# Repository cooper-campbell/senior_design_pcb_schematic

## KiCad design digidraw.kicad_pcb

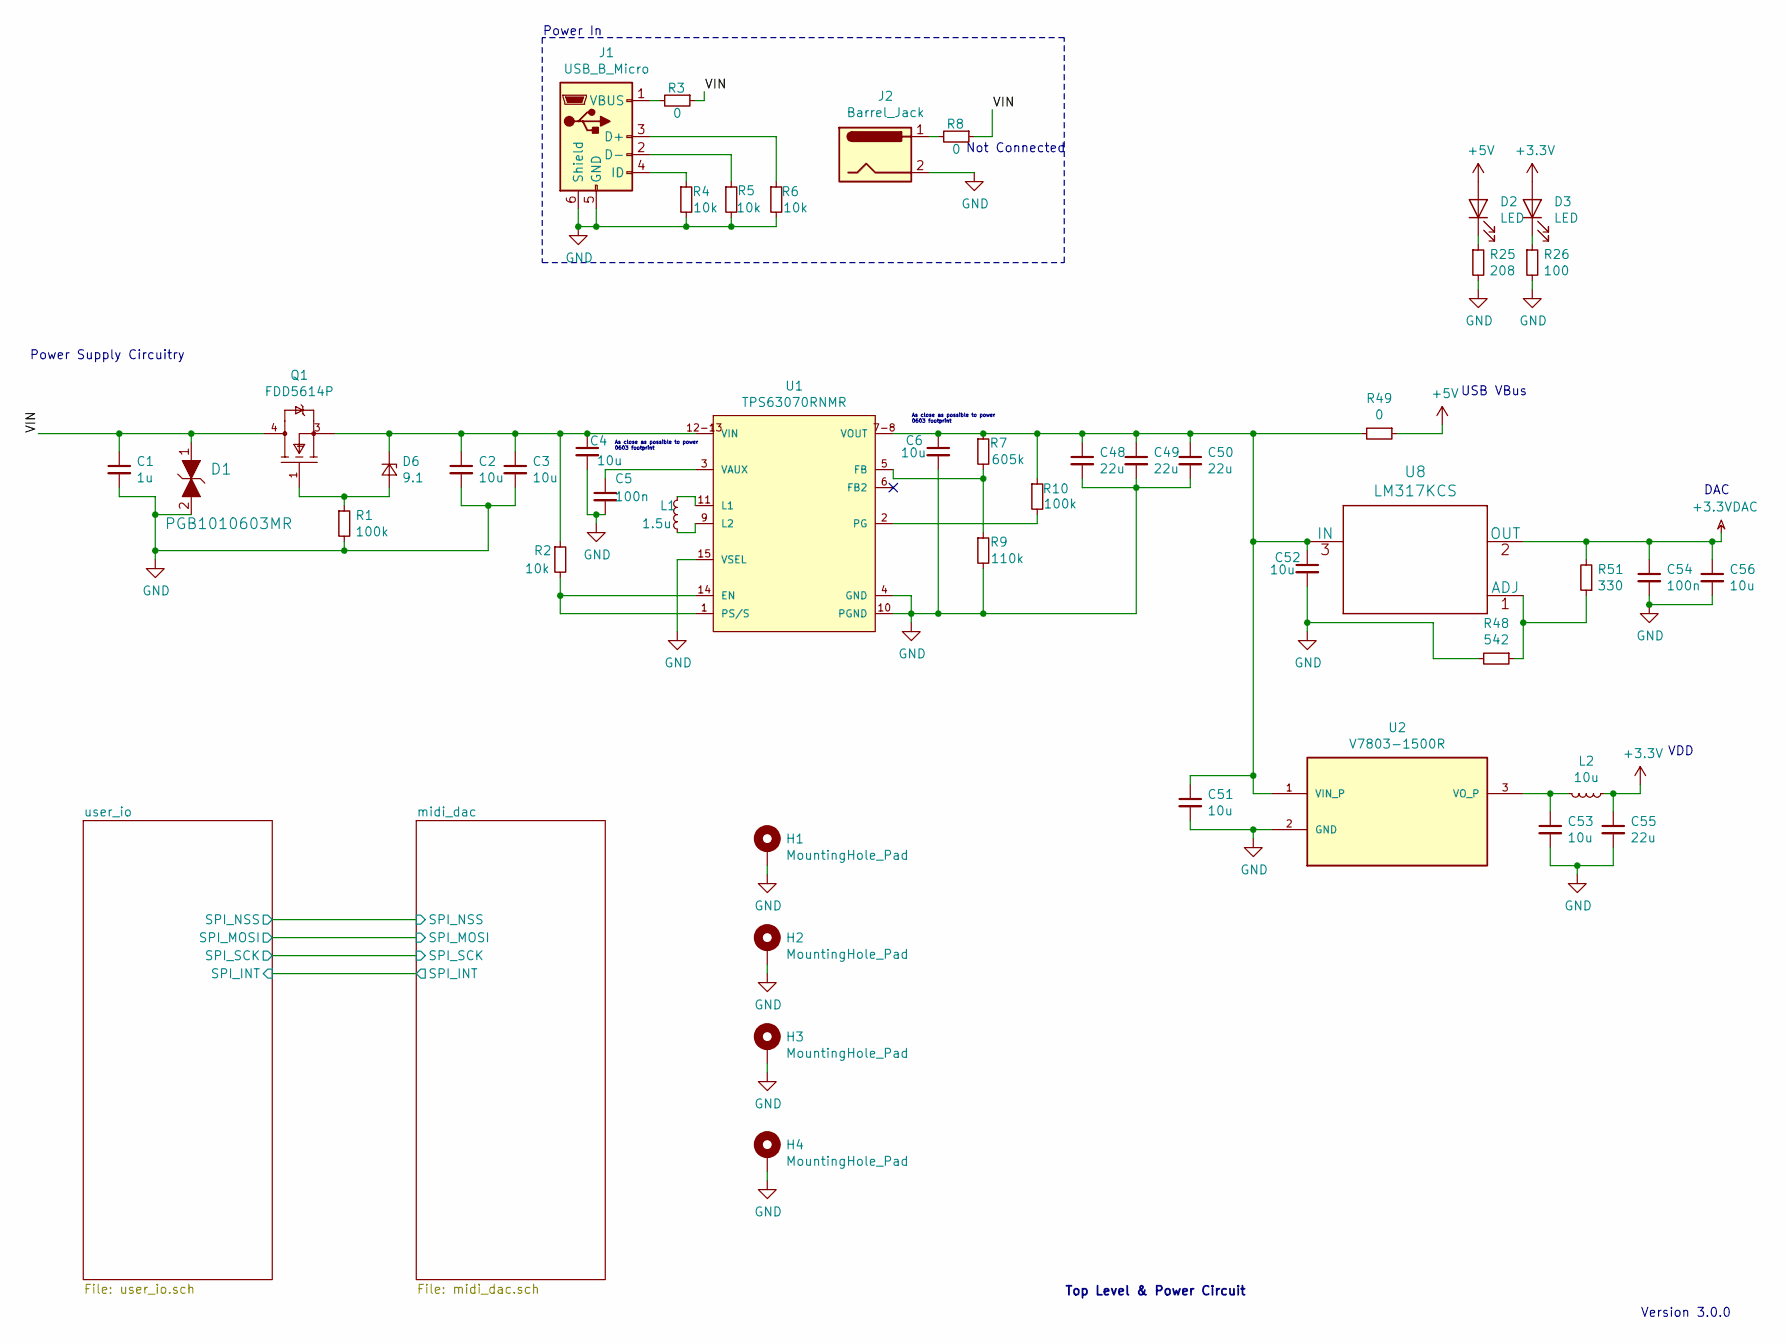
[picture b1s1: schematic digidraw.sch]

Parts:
C1: 1u; C_0805_2012Metric; Min Voltage Rating 16 V
C2, C3: 10u; C_0805_2012Metric; Min Voltage Rating 16 V
C4: 10u; C_0603_1608Metric; Min Voltage Rating 16 V
C5: 100n; C_0805_2012Metric; Min Voltage Rating 16 V
C6: 10u; C_0603_1608Metric; Min Voltage Rating 5.2 V
C48, C49, C50: 22u; C_0805_2012Metric; Min Voltage Rating 5.2 V
C51, C53: 10u; C_0603_1608Metric
C52: 10u; C_0805_2012Metric; Min Voltage Rating 5.2 V
C54: 100n; C_0805_2012Metric; Min Voltage Rating 3.3 V
C55: 22u; C_0603_1608Metric; Min Voltage Rating 3.3 V
C56: 10u; C_0603_1608Metric; Min Voltage Rating 3.3 V
D1: PGB1010603MR; 0603; MPN PGB1010603MR; Digi-Key_PN F2594CT-ND
D2, D3: LED; LED_0603_1608Metric; Digi-Key_PN AA1608SURSK
D6: 9.1; D_0603_1608Metric; Digi-Key_PN CDBU0320
H1, H2, H3, H4: MountingHole_Pad; MountingHole_4.3mm_M4_Pad_Via
J1: USB_B_Micro; USB_Micro-B_Molex-105017-0001; Digi-Key_PN 105017-0001
J2: Barrel_Jack; Barrel_Jack_5.5mmODx2.1mmID_PJ-202A; Digi-Key_PN PJ-202A
L1: 1.5u; InductorWEPD; Digi-Key_PN 7447707015
L2: 10u; L_0603_1608Metric; Digi-Key_PN MLZ1608E100MT
Q1: FDD5614P; ON_Semi-369AS-09_2016-O-0; mouser part number 512-FDD5614P; digikey description MOSFET P-CH 60V 15A DPAK
R1, R10: 100k; R_0603_1608Metric
R2, R4, R5, R6: 10k; R_0603_1608Metric
R3, R8, R49: 0; R_0603_1608Metric
R7: 605k; R_0603_1608Metric
R9: 110k; R_0603_1608Metric
R25: 208; R_0603_1608Metric
R26: 100; R_0603_1608Metric
R48: 542; R_0603_1608Metric
R51: 330; R_0603_1608Metric
U1: TPS63070RNMR; Texas_Instruments-RNM0015A-0-0-MFG; output voltage 2.5-9V; mouser part number 595-TPS63070RNMR; digikey description IC REG BCK BST ADJ 3.6A 15VQFN
U2: V7803-1500R; CONV_V7803-1500R; PARTREV 1.03; Digi-Key_PN V7803-1500R
U8: LM317KCS; Digi-Key_PN LM317KCS

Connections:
+3.3VDAC: C54.1, C56.1, R51.2, U8.2 (OUT); also elsewhere on the board
+3V3: C55.1, D3.2 (A), L2.1; also elsewhere on the board
+5V: D2.2 (A), R49.1; also elsewhere on the board
/VIN: C1.1, D1.1, Q1.4 (D), R3.1, R8.1
GND: C1.2, C2.2, C3.2, C4.2, C5.2, C6.2, C48.2, C49.2, C50.2, C51.2, C52.2, C53.2, C54.2, C55.2, C56.2, D1.2, H1.1, H2.1, H3.1, H4.1, J1.5 (GND), J1.6 (Shield), J2.2, R1.2, R4.2, R5.2, R6.2, R9.2, R25.2, R26.2, R48.2, U1.4 (GND), U1.10 (PGND), U1.15 (VSEL), U2.2 (GND); also elsewhere on the board
unnamed: C2.1, C3.1, C4.1, D6.1 (K), Q1.3 (S), R2.1, U1.12-13 (VIN)
unnamed: C5.1, U1.3 (VAUX)
unnamed: C6.1, C48.1, C49.1, C50.1, C51.1, C52.1, R7.1, R10.1, R49.2, U1.7-8 (VOUT), U2.1 (VIN_P), U8.3 (IN)
unnamed: C53.1, L2.2, U2.3 (VO_P)
unnamed: D2.1 (K), R25.1
unnamed: D3.1 (K), R26.1
unnamed: D6.2 (A), Q1.1 (G), R1.1
unnamed: J1.1 (VBUS), R3.2
unnamed: J1.2 (D-), R5.1
unnamed: J1.3 (D+), R6.1
unnamed: J1.4 (ID), R4.1
unnamed: J2.1, R8.2
unnamed: L1.1, U1.9 (L2)
unnamed: L1.2, U1.11 (L1)
unnamed: R2.2, U1.1 (PS/S), U1.14 (EN)
unnamed: R7.2, R9.1, U1.5 (FB)
unnamed: R10.2, U1.2 (PG)
unnamed: R48.1, R51.1, U8.1 (ADJ)

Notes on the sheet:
Power In
Top Level & Power Circuit
Version 3.0.0
Not Connected
As close as possible to power 0603 footprint
USB VBus
VDD
DAC
Power Supply Circuitry

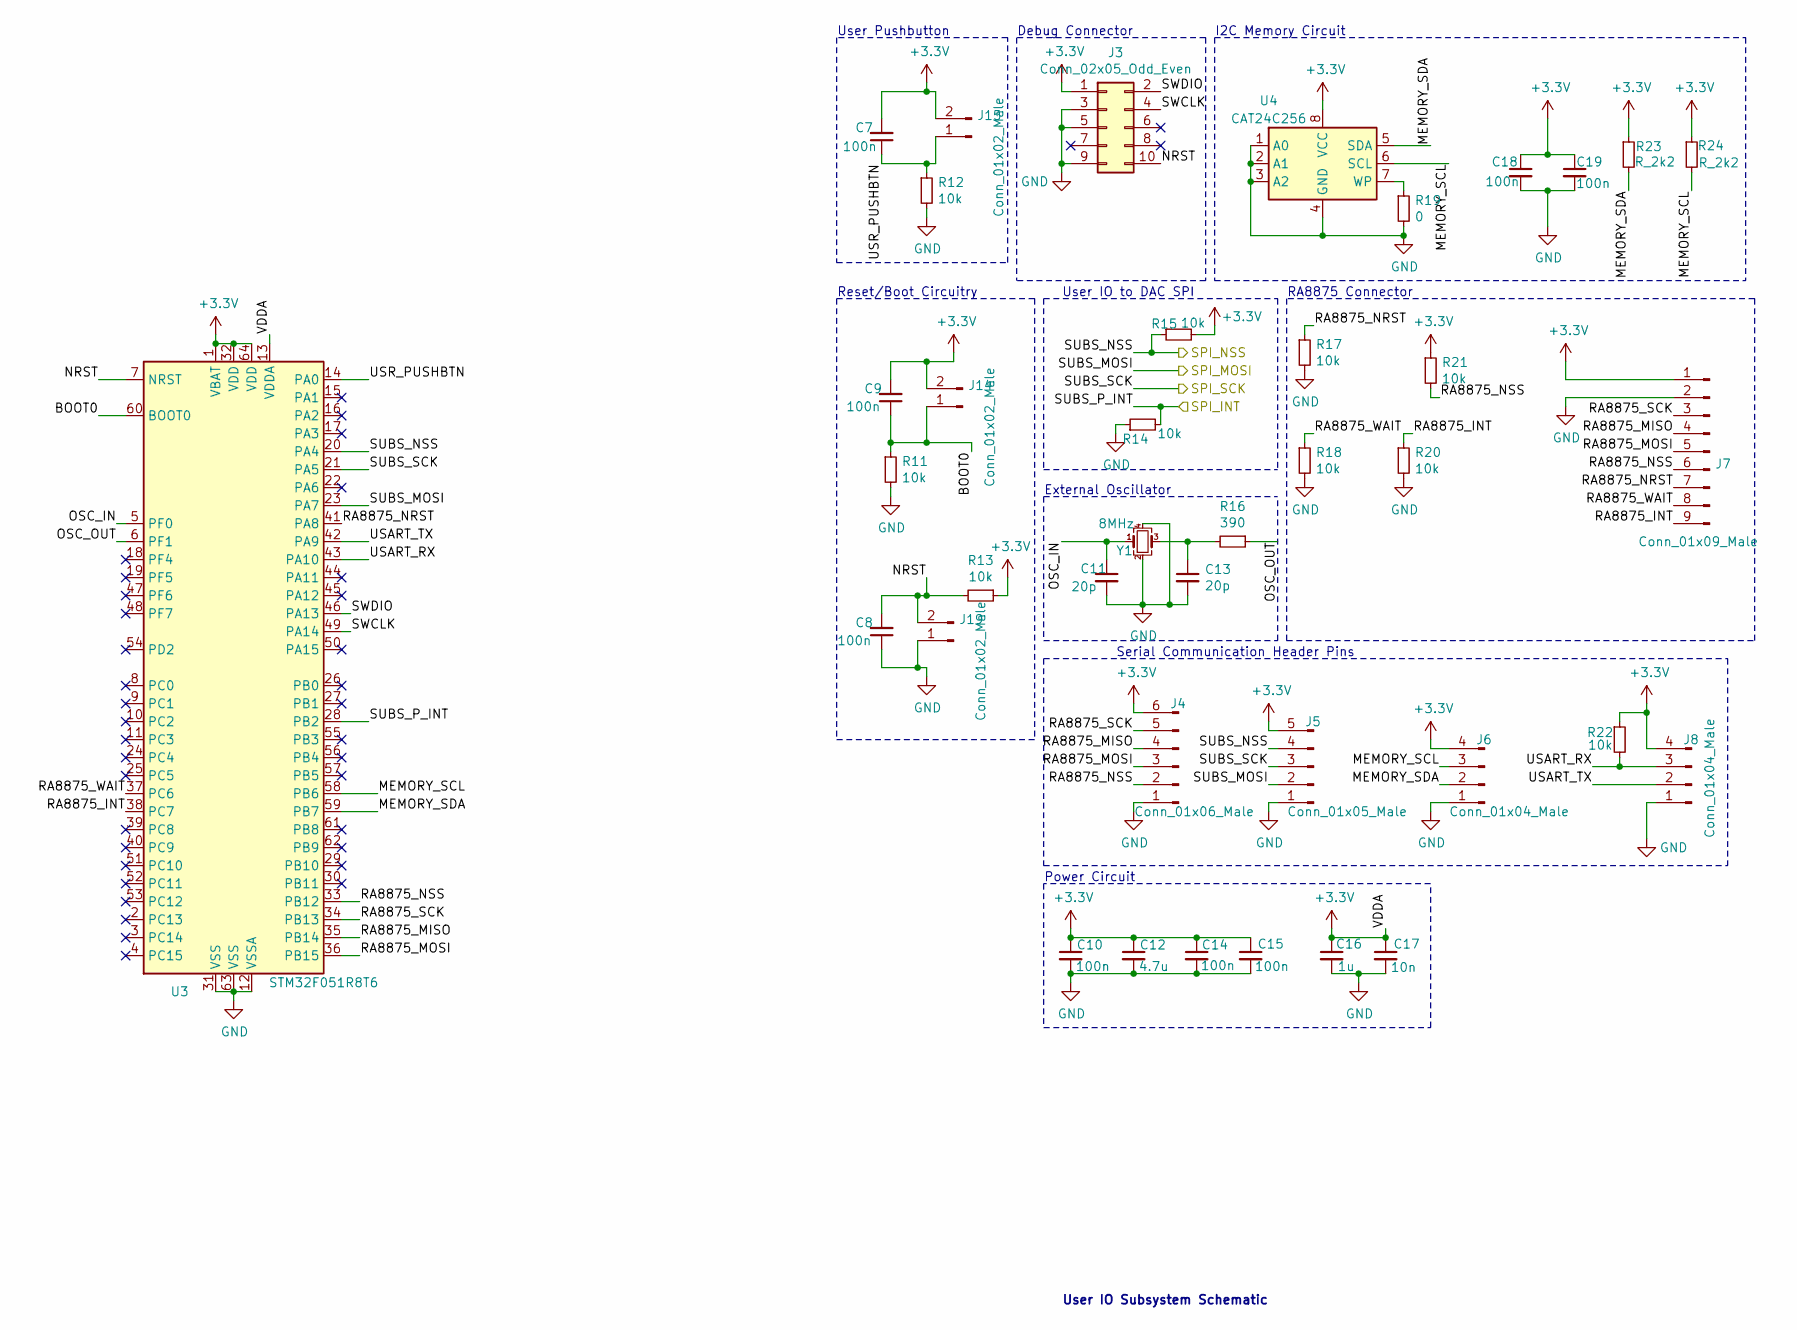
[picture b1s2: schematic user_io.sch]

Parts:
C7, C8, C9: 100n; C_0805_2012Metric; Min Voltage Rating 3.3 V
C10, C14, C15, C18, C19: 100n; C_0603_1608Metric; Min Voltage Rating 3.3 V
C11, C13: 20p; C_0603_1608Metric; Min Voltage Rating 3.3 V
C12: 4.7u; C_0603_1608Metric; Min Voltage Rating 3.3 V
C16: 1u; C_0603_1608Metric; Min Voltage Rating 3.3 V
C17: 10n; C_0603_1608Metric
J3: Conn_02x05_Odd_Even; PinHeader_2x05_P1.27mm_Vertical_SMD
J4: Conn_01x06_Male; PinHeader_1x06_P2.54mm_Vertical
J5: Conn_01x05_Male; PinHeader_1x05_P2.54mm_Vertical
J6, J8: Conn_01x04_Male; PinHeader_1x04_P2.54mm_Vertical
J7: Conn_01x09_Male; PinHeader_1x09_P2.54mm_Vertical
J14, J15, J19: Conn_01x02_Male; PinHeader_1x02_P2.54mm_Vertical
R11, R12, R13, R14, R15, R17, R18, R20, R21, R22: 10k; R_0603_1608Metric
R16: 390; R_0603_1608Metric
R19: 0; R_0603_1608Metric
R23, R24: R_2k2; R_0603_1608Metric
U3: STM32F051R8T6; LQFP-64_10x10mm_P0.5mm; Digi-Key_PN STM32F051R8T6
U4: CAT24C256; TSSOP-8_4.4x3mm_P0.65mm; Digi-Key_PN CAT24C256YI-GT3
Y1: 8MHz; Crystal_SMD_Abracon_ABM10-4Pin_2.5x2.0mm; Digi-Key_PN ASDDV-8.000MHZ-LR-T

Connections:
+3V3: C7.2, C9.2, C10.1, C12.1, C14.1, C15.1, C16.1, C17.1, C18.1, C19.1, J3.1, J4.6, J5.5, J6.4, J7.1, J8.4, J14.2, J15.2, R13.1, R15.2, R21.1, R22.1, R23.1, R24.1, U3.1 (VBAT), U3.13 (VDDA), U3.32 (VDD), U3.64 (VDD), U4.8 (VCC); also elsewhere on the board
/midi_dac/SPI_INT: R14.2, U3.28 (PB2); also elsewhere on the board
/midi_dac/SPI_MOSI: J5.2, U3.23 (PA7); also elsewhere on the board
/midi_dac/SPI_NSS: J5.4, R15.1, U3.20 (PA4); also elsewhere on the board
/midi_dac/SPI_SCK: J5.3, U3.21 (PA5); also elsewhere on the board
/user_io/BOOT0: C9.1, J14.1, R11.1, U3.60 (BOOT0)
/user_io/MEMORY_SCL: J6.3, R24.2, U3.58 (PB6), U4.6 (SCL)
/user_io/MEMORY_SDA: J6.2, R23.2, U3.59 (PB7), U4.5 (SDA)
/user_io/NRST: C8.2, J3.10, J19.2, R13.2, U3.7 (NRST)
/user_io/OSC_IN: C11.1, U3.5 (PF0), Y1.1
/user_io/OSC_OUT: R16.1, U3.6 (PF1)
/user_io/RA8875_INT: J7.9, R20.1, U3.38 (PC7)
/user_io/RA8875_MISO: J4.4, J7.4, U3.35 (PB14)
/user_io/RA8875_MOSI: J4.3, J7.5, U3.36 (PB15)
/user_io/RA8875_NRST: J7.7, R17.1, U3.41 (PA8)
/user_io/RA8875_NSS: J4.2, J7.6, R21.2, U3.33 (PB12)
/user_io/RA8875_SCK: J4.5, J7.3, U3.34 (PB13)
/user_io/RA8875_WAIT: J7.8, R18.1, U3.37 (PC6)
/user_io/SWCLK: J3.4, U3.49 (PA14)
/user_io/SWDIO: J3.2, U3.46 (PA13)
/user_io/USART_RX: J8.3, R22.2, U3.43 (PA10)
/user_io/USART_TX: J8.2, U3.42 (PA9)
/user_io/USR_PUSHBTN: C7.1, J15.1, R12.1, U3.14 (PA0)
GND: C8.1, C10.2, C11.2, C12.2, C13.2, C14.2, C15.2, C16.2, C17.2, C18.2, C19.2, J3.3, J3.5, J3.9, J4.1, J5.1, J6.1, J7.2, J8.1, J19.1, R11.2, R12.2, R14.1, R17.2, R18.2, R19.2, R20.2, U3.12 (VSSA), U3.31 (VSS), U3.63 (VSS), U4.1 (A0), U4.2 (A1), U4.3 (A2), U4.4 (GND), Y1.2, Y1.4; also elsewhere on the board
unnamed: C13.1, R16.2, Y1.3
unnamed: R19.1, U4.7 (WP)

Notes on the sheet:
I2C Memory Circuit
User IO to DAC SPI
RA8875 Connector
User IO Subsystem Schematic
Reset/Boot Circuitry
Debug Connector
Power Circuit
Serial Communication Header Pins
External Oscillator
User Pushbutton

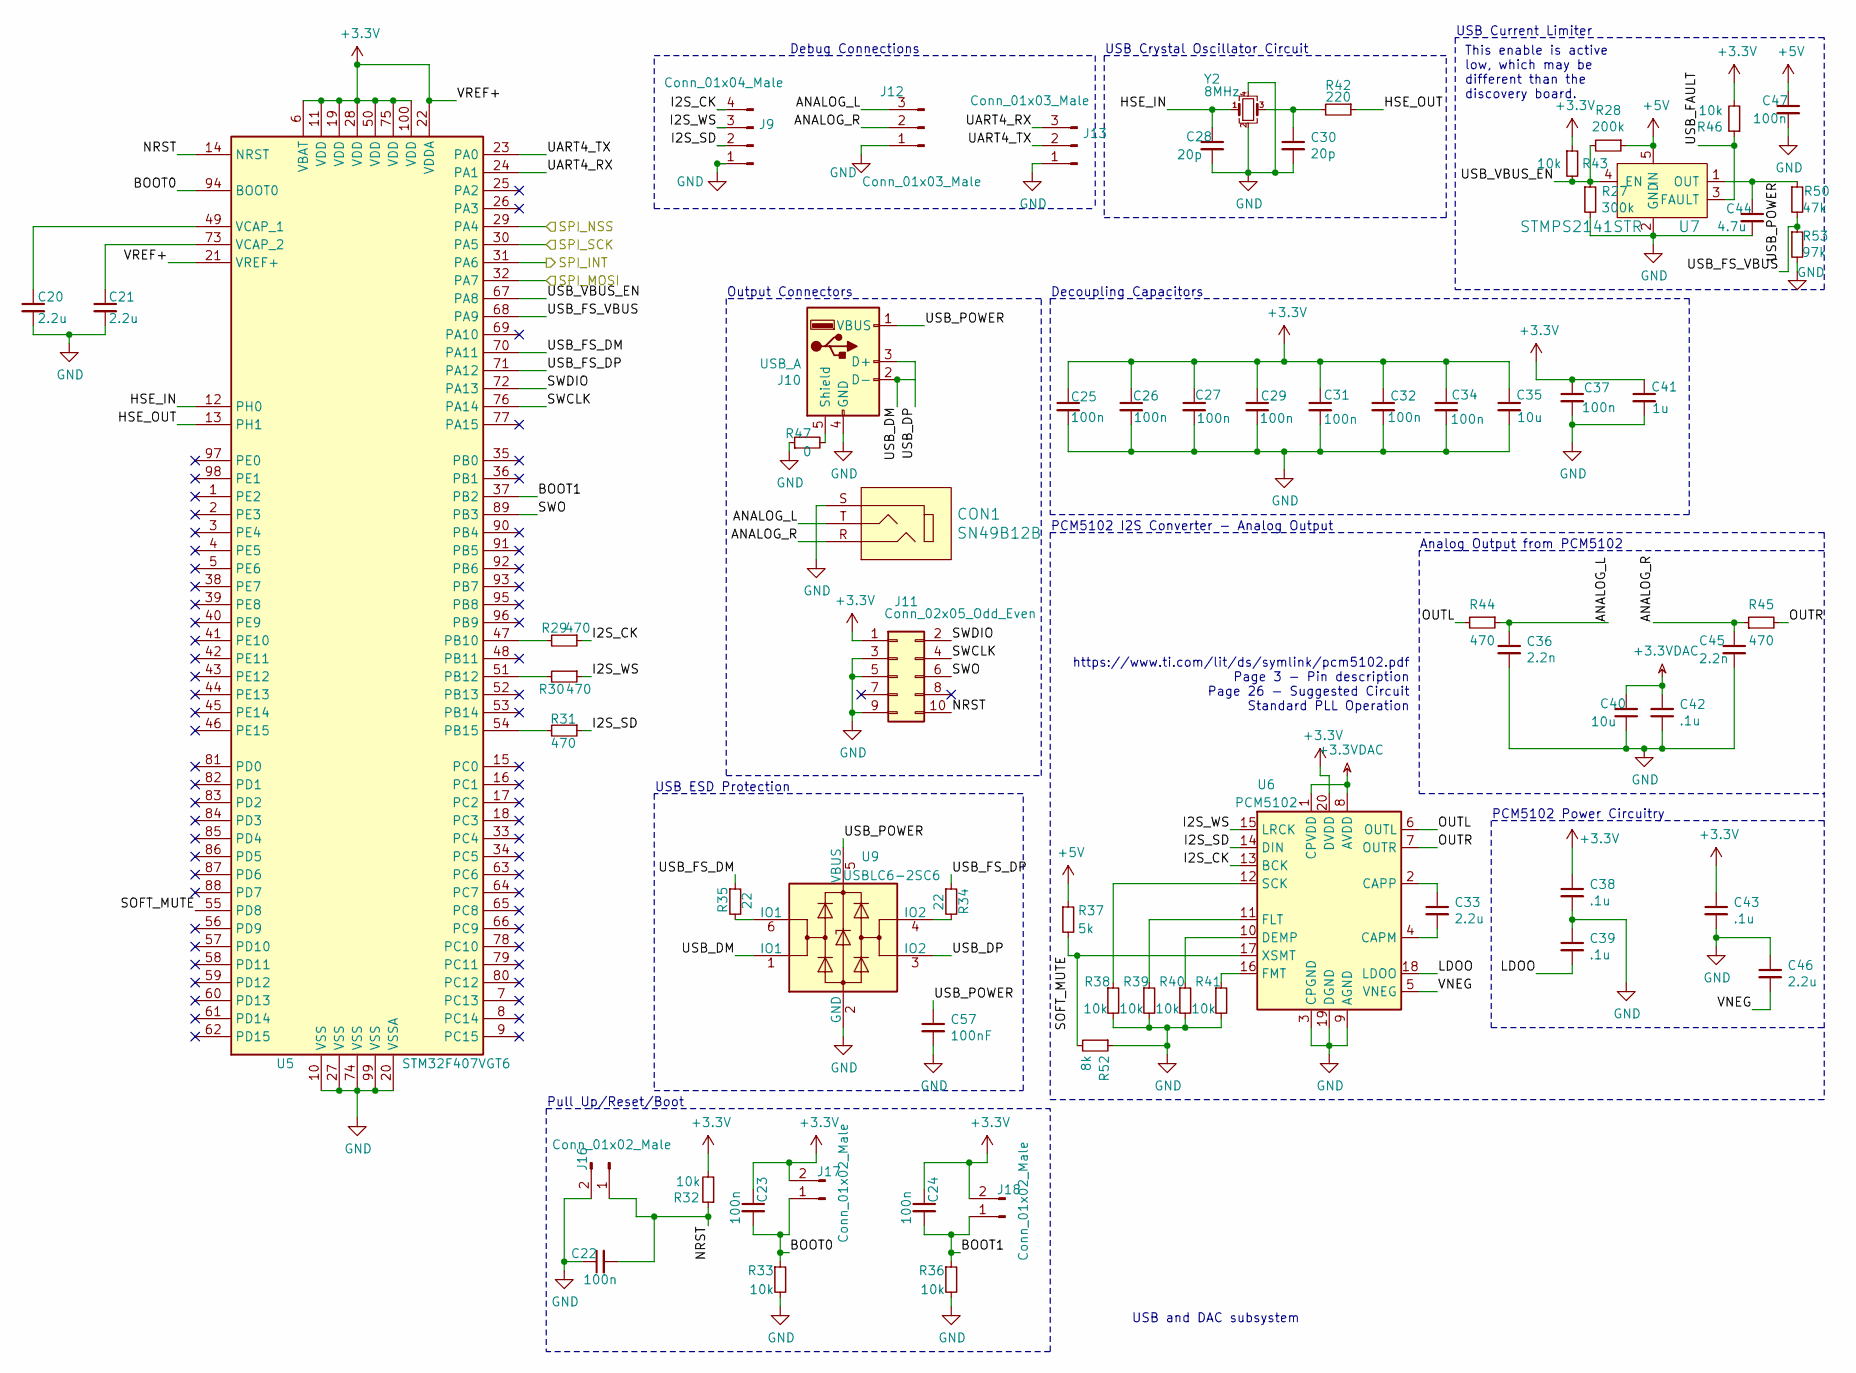
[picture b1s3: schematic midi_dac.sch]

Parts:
C20, C21, C46: 2.2u; C_0805_2012Metric; Min Voltage Rating 3.3 V
C22, C23, C24, C25, C26, C27, C29, C31, C32, C34, C37: 100n; C_0805_2012Metric; Min Voltage Rating 3.3 V
C28, C30: 20p; C_0603_1608Metric; Min Voltage Rating 3.3 V
C33: 2.2u; C_0603_1608Metric; Min Voltage Rating 3.3 V
C35: 10u; C_0603_1608Metric; Min Voltage Rating 3.3 V
C36, C45: 2.2n; C_0805_2012Metric; Min Voltage Rating 3.3 V
C38, C39, C42, C43: .1u; C_0603_1608Metric; Min Voltage Rating 3.3 V
C40: 10u; C_0805_2012Metric; Min Voltage Rating 3.3 V
C41: 1u; C_0603_1608Metric; Min Voltage Rating 3.3 V
C44: 4.7u; C_0805_2012Metric; Min Voltage Rating 5.2 V
C47: 100n; C_0805_2012Metric; Min Voltage Rating 5.2 V
C57: 100nF; C_0805_2012Metric; Min Voltage Rating 5.2 V
CON1: SN49B12B; Headphone_Jack_6.35mm_SN49B12B; MPN SN49B12B; Digi-Key_PN SC1522-ND
J9: Conn_01x04_Male; PinHeader_1x04_P2.54mm_Vertical
J10: USB_A; USB_A_Molex_67643_Horizontal; Digi-Key_PN 67643-3910
J11: Conn_02x05_Odd_Even; PinHeader_2x05_P1.27mm_Vertical_SMD
J12, J13: Conn_01x03_Male; PinHeader_1x03_P2.54mm_Vertical
J16, J17, J18: Conn_01x02_Male; PinHeader_1x02_P2.54mm_Vertical
R27: 300k; R_0603_1608Metric
R28: 200k; R_0603_1608Metric
R29, R30, R31, R44, R45: 470; R_0603_1608Metric
R32, R33, R36, R38, R39, R40, R41, R43, R46: 10k; R_0603_1608Metric
R34, R35: 22; R_0603_1608Metric
R37: 5k; R_0603_1608Metric
R42: 220; R_0603_1608Metric
R47: 0; R_0603_1608Metric
R50: 47k; R_0603_1608Metric
R52: 8k; R_0603_1608Metric
R53: 97k; R_0603_1608Metric
U5: STM32F407VGT6; LQFP-100_14x14mm_P0.5mm; Digi-Key_PN STM32F407VGT6
U6: PCM5102; TSSOP-20_4.4x6.5mm_P0.65mm; Digi-Key_PN PCM5102APWR
U7: STMPS2141STR; SOT-753; MPN STMPS2141STR; Digi-Key_PN 497-6933-1-ND
U9: USBLC6-2SC6; SOT-23-6; Digi-Key_PN USBLC6-2SC6
Y2: 8MHz; Crystal_SMD_Abracon_ABM10-4Pin_2.5x2.0mm; Digi-Key_PN ASDDV-8.000MHZ-LR-T

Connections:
+3.3VDAC: C40.2, C42.2, U6.1 (CPVDD), U6.8 (AVDD); also elsewhere on the board
+3V3: C23.1, C24.1, C25.1, C26.1, C27.1, C29.1, C31.1, C32.1, C34.1, C35.1, C37.1, C38.1, C41.1, C43.1, J11.1, J17.2, J18.2, R32.2, R43.1, R46.2, U5.6 (VBAT), U5.11 (VDD), U5.19 (VDD), U5.21 (VREF+), U5.22 (VDDA), U5.28 (VDD), U5.50 (VDD), U5.75 (VDD), U5.100 (VDD), U6.20 (DVDD); also elsewhere on the board
+5V: C47.1, R28.1, R37.1, U7.5 (IN); also elsewhere on the board
/midi_dac/ANALOG_L: C36.1, CON1.T, J12.3, R44.1
/midi_dac/ANALOG_R: C45.1, CON1.R, J12.2, R45.1
/midi_dac/BOOT0: C23.2, J17.1, R33.1, U5.94 (BOOT0)
/midi_dac/BOOT1: C24.2, J18.1, R36.1, U5.37 (PB2)
/midi_dac/HSE_IN: C28.1, U5.12 (PH0), Y2.1
/midi_dac/HSE_OUT: R42.1, U5.13 (PH1)
/midi_dac/I2S_CK: J9.4, R29.1, U6.13 (BCK)
/midi_dac/I2S_SD: J9.2, R31.1, U6.14 (DIN)
/midi_dac/I2S_WS: J9.3, R30.1, U6.15 (LRCK)
/midi_dac/LDOO: C39.2, U6.18 (LDOO)
/midi_dac/NRST: C22.2, J11.10, J16.1, R32.1, U5.14 (NRST)
/midi_dac/OUTL: R44.2, U6.6 (OUTL)
/midi_dac/OUTR: R45.2, U6.7 (OUTR)
/midi_dac/SOFT_MUTE: R37.2, R52.2, U5.55 (PD8), U6.17 (XSMT)
/midi_dac/SPI_INT: U5.31 (PA6); also elsewhere on the board
/midi_dac/SPI_MOSI: U5.32 (PA7); also elsewhere on the board
/midi_dac/SPI_NSS: U5.29 (PA4); also elsewhere on the board
/midi_dac/SPI_SCK: U5.30 (PA5); also elsewhere on the board
/midi_dac/SWCLK: J11.4, U5.76 (PA14)
/midi_dac/SWDIO: J11.2, U5.72 (PA13)
/midi_dac/SWO: J11.6, U5.89 (PB3)
/midi_dac/UART4_RX: J13.3, U5.24 (PA1)
/midi_dac/UART4_TX: J13.2, U5.23 (PA0)
/midi_dac/USB_DM: J10.2 (D-), U9.1 (IO1)
/midi_dac/USB_DP: J10.3 (D+), U9.3 (IO2)
/midi_dac/USB_FAULT: R46.1, U7.3 (FAULT)
/midi_dac/USB_FS_DM: R35.1, U5.70 (PA11)
/midi_dac/USB_FS_DP: R34.1, U5.71 (PA12)
/midi_dac/USB_FS_VBUS: R50.2, R53.1, U5.68 (PA9)
/midi_dac/USB_POWER: C44.1, C57.1, J10.1 (VBUS), R50.1, U7.1 (OUT), U9.5 (VBUS)
/midi_dac/USB_VBUS_EN: R27.1, R28.2, R43.2, U5.67 (PA8), U7.4 (EN)
/midi_dac/VNEG: C46.2, U6.5 (VNEG)
GND: C20.2, C21.2, C22.1, C25.2, C26.2, C27.2, C28.2, C29.2, C30.2, C31.2, C32.2, C34.2, C35.2, C36.2, C37.2, C38.2, C39.1, C40.1, C41.2, C42.1, C43.2, C44.2, C45.2, C46.1, C47.2, C57.2, CON1.S, J9.1, J10.4 (GND), J11.3, J11.5, J11.9, J12.1, J13.1, J16.2, R27.2, R33.2, R36.2, R38.2, R39.2, R40.2, R41.2, R47.1, R52.1, R53.2, U5.10 (VSS), U5.20 (VSSA), U5.27 (VSS), U5.74 (VSS), U5.99 (VSS), U6.3 (CPGND), U6.9 (AGND), U6.19 (DGND), U7.2 (GND), U9.2 (GND), Y2.2, Y2.4; also elsewhere on the board
unnamed: C20.1, U5.49 (VCAP_1)
unnamed: C21.1, U5.73 (VCAP_2)
unnamed: C30.1, R42.2, Y2.3
unnamed: C33.1, U6.2 (CAPP)
unnamed: C33.2, U6.4 (CAPM)
unnamed: J10.5 (Shield), R47.2
unnamed: R29.2, U5.47 (PB10)
unnamed: R30.2, U5.51 (PB12)
unnamed: R31.2, U5.54 (PB15)
unnamed: R34.2, U9.4 (IO2)
unnamed: R35.2, U9.6 (IO1)
unnamed: R38.1, U6.12 (SCK)
unnamed: R39.1, U6.11 (FLT)
unnamed: R40.1, U6.10 (DEMP)
unnamed: R41.1, U6.16 (FMT)

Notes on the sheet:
Decoupling Capacitors
USB Crystal Oscillator Circuit
https://www.ti.com/lit/ds/symlink/pcm5102.pdf Page 3 - Pin description Page 26 - Suggested Circuit Standard PLL Operation
Analog Output from PCM5102
PCM5102 Power Circuitry
PCM5102 I2S Converter - Analog Output
This enable is active low, which may be different than the discovery board.
USB Current Limiter
Pull Up/Reset/Boot
Output Connectors
USB and DAC subsystem
Debug Connections
USB ESD Protection

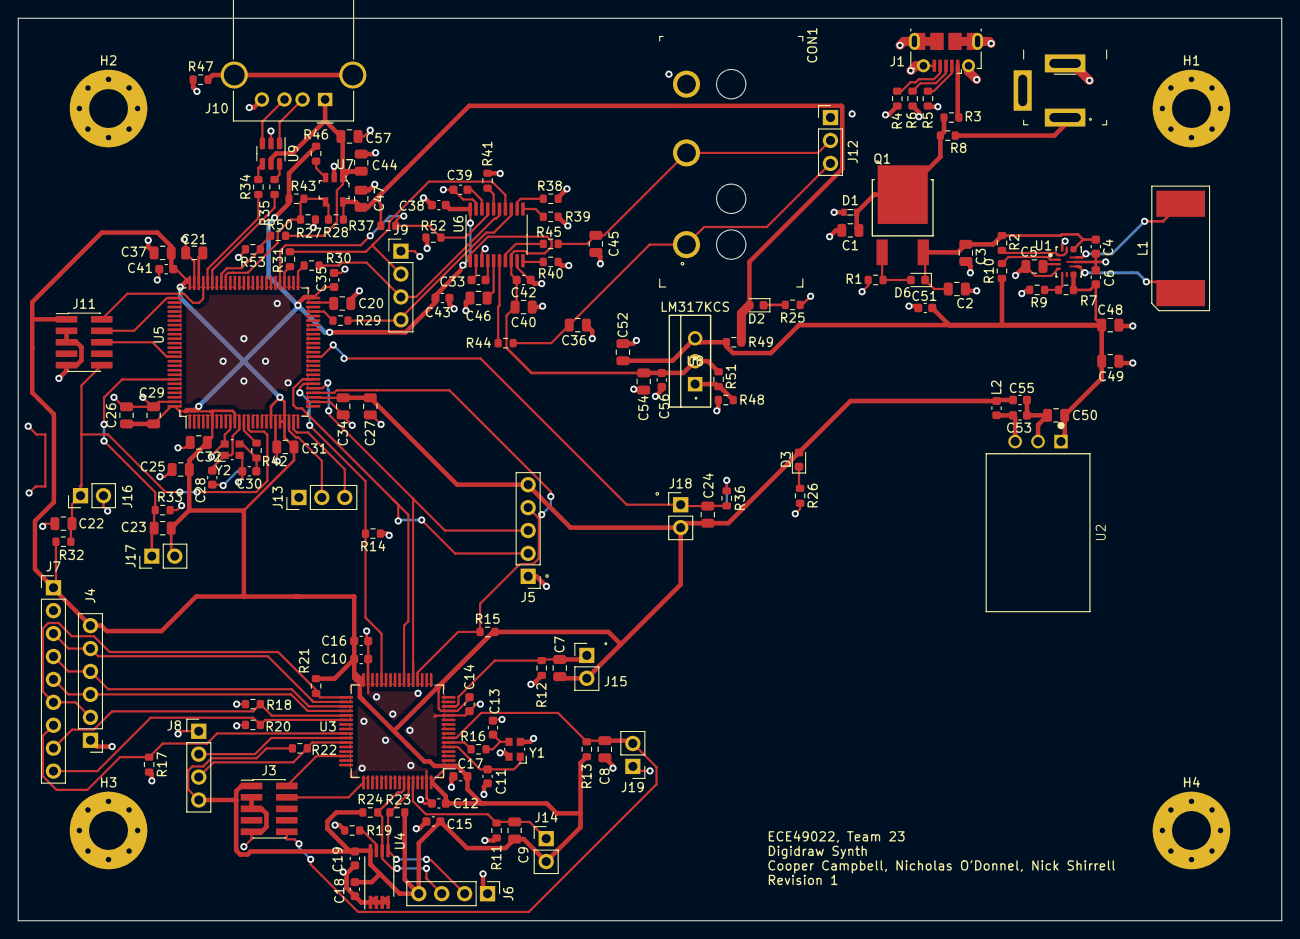
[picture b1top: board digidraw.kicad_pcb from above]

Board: 2 copper layers, 140.0 x 100.0 mm, 152 parts (0 on the bottom side), 90 nets.

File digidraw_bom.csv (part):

Tool:,Eeschema 5.1.9,,,,,,,,,,,,,,,,,,,,,,,,,,,,,,,,,,,,,,,,,,,,,,,,,,,,,,,,,,,,
Generator:,/usr/share/kicad/plugins/bom_csv_grouped_by_value.py,,,,,,,,,,,,,,,,,,,,,,,,,,,,,,,,,,,,,,,,,,,,,,,,,,,,,,,,,,,,
Component Count:,152,,,,,,,,,,,,,,,,,,,,,,,,,,,,,,,,,,,,,,,,,,,,,,,,,,,,,,,,,,,,
,,,,,,,,,,,,,,,,,,,,,,,,,,,,,,,,,,,,,,,,,,,,,,,,,,,,,,,,,,,,,
Individual Components:,,,,,,,,,,,,,,,,,,,,,,,,,,,,,,,,,,,,,,,,,,,,,,,,,,,,,,,,,,,,,
,,,,,,,,,,,,,,,,,,,,,,,,,,,,,,,,,,,,,,,,,,,,,,,,,,,,,,,,,,,,,
Collated Components:,,,,,,,,,,,,,,,,,,,,,,,,,,,,,,,,,,,,,,,,,,,,,,,,,,,,,,,,,,,,,
,,,,,,,,,,,,,,,,,,,,,,,,,,,,,,,,,,,,,,,,,,,,,,,,,,,,,,,,,,,,,
Item,Qty,Reference(s),Value,Part Number,LibPart,Footprint,Datasheet,Category,DK_Datasheet_Link,DK_Detail_Page,Description,Family,MANUFACTURER,MPN,Manufacturer,Min Voltage Rating,PARTREV,STANDARD,Status,automotive,category,continuous drain current,device class L1,device class L2,device class L3,digikey description,digikey part number,drain to source breakdown voltage,drain to source resistance,drain to source voltage,footprint url,gate to source voltage,height,input capacitace at vds,lead free,library id,manufacturer,max duty cycle,max junction temp,max supply voltage,min supply voltage,mouser part number,nominal supply current,number of P channels,number of channels,number of outputs,output current,output type,output voltage,package,power dissipation,rohs,standoff height,switching frequency,switching topology,technology,temperature range high,temperature range low,threshold vgs,turn off delay time,turn on delay time
1,1,C1,1u,,Device:C_Small,Capacitor_SMD:C_0805_2012Metric,~,,,,,,,,,16 V,,,,,,,,,,,,,,,,,,,,,,,,,,,,,,,,,,,,,,,,,,,,,
2,4,"C2, C3, C40, C52",10u,,Device:C_Small,Capacitor_SMD:C_0805_2012Metric,~,,,,,,,,,16 V,,,,,,,,,,,,,,,,,,,,,,,,,,,,,,,,,,,,,,,,,,,,,
3,6,"C4, C6, C35, C51, C53, C56",10u,,Device:C_Small,Capacitor_SMD:C_0603_1608Metric,~,,,,,,,,,16 V,,,,,,,,,,,,,,,,,,,,,,,,,,,,,,,,,,,,,,,,,,,,,
4,17,"C5, C7, C8, C9, C22, C23, C24, C25, C26, C27, C29, C31, C32, C34, C37, C47, C54",100n,,Device:C_Small,Capacitor_SMD:C_0805_2012Metric,~,,,,,,,,,16 V,,,,,,,,,,,,,,,,,,,,,,,,,,,,,,,,,,,,,,,,,,,,,
5,5,"C10, C14, C15, C18, C19",100n,,Device:C_Small,Capacitor_SMD:C_0603_1608Metric,~,,,,,,,,,3.3 V,,,,,,,,,,,,,,,,,,,,,,,,,,,,,,,,,,,,,,,,,,,,,
6,4,"C11, C13, C28, C30",20p,,Device:C_Small,Capacitor_SMD:C_0603_1608Metric,~,,,,,,,,,3.3 V,,,,,,,,,,,,,,,,,,,,,,,,,,,,,,,,,,,,,,,,,,,,,
7,1,C12,4.7u,,Device:C_Small,Capacitor_SMD:C_0603_1608Metric,~,,,,,,,,,3.3 V,,,,,,,,,,,,,,,,,,,,,,,,,,,,,,,,,,,,,,,,,,,,,
8,2,"C16, C41",1u,,Device:C_Small,Capacitor_SMD:C_0603_1608Metric,~,,,,,,,,,3.3 V,,,,,,,,,,,,,,,,,,,,,,,,,,,,,,,,,,,,,,,,,,,,,
9,1,C17,10n,,Device:C_Small,Capacitor_SMD:C_0603_1608Metric,~,,,,,,,,,,,,,,,,,,,,,,,,,,,,,,,,,,,,,,,,,,,,,,,,,,,,,,
10,3,"C20, C21, C46",2.2u,,Device:C_Small,Capacitor_SMD:C_0805_2012Metric,~,,,,,,,,,3.3 V,,,,,,,,,,,,,,,,,,,,,,,,,,,,,,,,,,,,,,,,,,,,,
11,1,C33,2.2u,,Device:C_Small,Capacitor_SMD:C_0603_1608Metric,~,,,,,,,,,3.3 V,,,,,,,,,,,,,,,,,,,,,,,,,,,,,,,,,,,,,,,,,,,,,
12,2,"C36, C45",2.2n,,Device:C_Small,Capacitor_SMD:C_0805_2012Metric,~,,,,,,,,,3.3 V,,,,,,,,,,,,,,,,,,,,,,,,,,,,,,,,,,,,,,,,,,,,,
13,4,"C38, C39, C42, C43",.1u,,Device:C_Small,Capacitor_SMD:C_0603_1608Metric,~,,,,,,,,,3.3 V,,,,,,,,,,,,,,,,,,,,,,,,,,,,,,,,,,,,,,,,,,,,,
14,1,C44,4.7u,,Device:C_Small,Capacitor_SMD:C_0805_2012Metric,~,,,,,,,,,5.2 V,,,,,,,,,,,,,,,,,,,,,,,,,,,,,,,,,,,,,,,,,,,,,
15,3,"C48, C49, C50",22u,,Device:C_Small,Capacitor_SMD:C_0805_2012Metric,~,,,,,,,,,5.2 V,,,,,,,,,,,,,,,,,,,,,,,,,,,,,,,,,,,,,,,,,,,,,
16,1,C55,22u,,Device:C_Small,Capacitor_SMD:C_0603_1608Metric,~,,,,,,,,,3.3 V,,,,,,,,,,,,,,,,,,,,,,,,,,,,,,,,,,,,,,,,,,,,,
17,1,C57,100nF,,Device:C_Small,Capacitor_SMD:C_0805_2012Metric,~,,,,,,,,,5.2 V,,,,,,,,,,,,,,,,,,,,,,,,,,,,,,,,,,,,,,,,,,,,,
18,1,CON1,SN49B12B,SC1522-ND,digidraw-rescue:SN49B12B-DIGIKEY_AUDIO_JACK,digikey-footprints:Headphone_Jack_6.35mm_SN49B12B,http://www.switchcraft.com/Drawings/SN49B_SERIES_CD.pdf,"Connectors, Interconnects",http://www.switchcraft.com/Drawings/SN49B_SERIES_CD.pdf,/product-detail/en/switchcraft-inc/SN49B12B/SC1522-ND/412780,CONN JACK STEREO 6.35MM R/A,Barrel - Audio Connectors,,SN49B12B,Switchcraft Inc.,,,,Active,,,,,,,,,,,,,,,,,,,,,,,,,,,,,,,,,,,,,,,,,,
19,1,D1,PGB1010603MR,F2594CT-ND,dk_TVS-Diodes:PGB1010603MR,digikey-footprints:0603,https://www.littelfuse.com/data/en/data_sheets/littelfuse_pu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,Circuit Protection,https://www.littelfuse.com/data/en/data_sheets/littelfuse_pu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,/product-detail/en/littelfuse-inc/PGB1010603MR/F2594CT-ND/813072,TVS DIODE 24V 150V 0603,TVS - Diodes,,PGB1010603MR,Littelfuse Inc.,,,,Active,,,,,,,,,,,,,,,,,,,,,,,,,,,,,,,,,,,,,,,,,,
20,2,"D2, D3",LED,AA1608SURSK,Device:LED,LED_SMD:LED_0603_1608Metric,~,,,,,,,,,,,,,,,,,,,,,,,,,,,,,,,,,,,,,,,,,,,,,,,,,,,,,,
21,1,D6,9.1,CDBU0320,Device:D_Zener_Small,Diode_SMD:D_0603_1608Metric,~,,,,Debug LED,,,,,,,,,,,,,,,,,,,,,,,,,,,,,,,,,,,,,,,,,,,,,,,,,,
22,4,"H1, H2, H3, H4",MountingHole_Pad,,Mechanical:MountingHole_Pad,MountingHole:MountingHole_4.3mm_M4_Pad_Via,~,,,,Mounting Holes,,,,,,,,,,,,,,,,,,,,,,,,,,,,,,,,,,,,,,,,,,,,,,,,,,
23,1,J1,USB_B_Micro,105017-0001,Connector:USB_B_Micro,Connector_USB:USB_Micro-B_Molex-105017-0001,~,,,,USB B micro for power,,,,,,,,,,,,,,,,,,,,,,,,,,,,,,,,,,,,,,,,,,,,,,,,,,
24,1,J2,Barrel_Jack,PJ-202A,Connector:Barrel_Jack,digikey-footprints:Barrel_Jack_5.5mmODx2.1mmID_PJ-202A,~,,,,Barrel jack for power (maybe),,,,,,,,,,,,,,,,,,,,,,,,,,,,,,,,,,,,,,,,,,,,,,,,,,
25,2,"J3, J11",Conn_02x05_Odd_Even,,Connector_Generic:Conn_02x05_Odd_Even,Connector_PinHeader_1.27mm:PinHeader_2x05_P1.27mm_Vertical_SMD,~,,,,,,,,,,,,,,,,,,,,,,,,,,,,,,,,,,,,,,,,,,,,,,,,,,,,,,
26,1,J4,Conn_01x06_Male,,Connector:Conn_01x06_Male,Connector_PinHeader_2.54mm:PinHeader_1x06_P2.54mm_Vertical,~,,,,Header for Screen SPI Debug,,,,,,,,,,,,,,,,,,,,,,,,,,,,,,,,,,,,,,,,,,,,,,,,,,
27,1,J5,Conn_01x05_Male,,Connector:Conn_01x05_Male,Connector_PinHeader_2.54mm:PinHeader_1x05_P2.54mm_Vertical,~,,,,Header for subsystem SPI Debug,,,,,,,,,,,,,,,,,,,,,,,,,,,,,,,,,,,,,,,,,,,,,,,,,,
28,3,"J6, J8, J9",Conn_01x04_Male,,Connector:Conn_01x04_Male,Connector_PinHeader_2.54mm:PinHeader_1x04_P2.54mm_Vertical,~,,,,Header for EEPROM I2C Debug,,,,,,,,,,,,,,,,,,,,,,,,,,,,,,,,,,,,,,,,,,,,,,,,,,
29,1,J7,Conn_01x09_Male,,Connector:Conn_01x09_Male,Connector_PinHeader_2.54mm:PinHeader_1x09_P2.54mm_Vertical,~,,,,,,,,,,,,,,,,,,,,,,,,,,,,,,,,,,,,,,,,,,,,,,,,,,,,,,
30,1,J10,USB_A,67643-3910,Connector:USB_A,Connector_USB:USB_A_Molex_67643_Horizontal, ~,,,,Connector for USB Midi,,,,,,,,,,,,,,,,,,,,,,,,,,,,,,,,,,,,,,,,,,,,,,,,,,
31,2,"J12, J13",Conn_01x03_Male,,Connector:Conn_01x03_Male,Connector_PinHeader_2.54mm:PinHeader_1x03_P2.54mm_Vertical,~,,,,Header for analog out probes,,,,,,,,,,,,,,,,,,,,,,,,,,,,,,,,,,,,,,,,,,,,,,,,,,
32,6,"J14, J15, J16, J17, J18, J19",Conn_01x02_Male,,Connector:Conn_01x02_Male,Connector_PinHeader_2.54mm:PinHeader_1x02_P2.54mm_Vertical,~,,,,,,,,,,,,,,,,,,,,,,,,,,,,,,,,,,,,,,,,,,,,,,,,,,,,,,
33,1,L1,1.5u,7447707015,Device:L_Small,custom_fp:InductorWEPD,~,,,,Buck/Boost converter inductor,,,,,,,,,,,,,,,,,,,,,,,,,,,,,,,,,,,,,,,,,,,,,,,,,,
34,1,L2,10u,MLZ1608E100MT,Device:L_Small,Inductor_SMD:L_0603_1608Metric,~,,,,,,,,,,,,,,,,,,,,,,,,,,,,,,,,,,,,,,,,,,,,,,,,,,,,,,
35,1,Q1,FDD5614P,FDD5614P,FDD5614P:FDD5614P,MOSFET_TI:ON_Semi-369AS-09_2016-O-0,http://www.onsemi.com/pub/Collateral/FDD5614P-D.PDF,,,,MOSFET for bias protection,,,,,,,,,,Trans,-15A,Discrete Semiconductors,Transistors,MOSFETs,MOSFET P-CH 60V 15A DPAK,FDD5614PCT-ND,-60V,76mΩ,-60V,http://www.onsemi.com/pub/Collateral/369AS.PDF,20V,2.39mm,759pF @ -30V,yes,36114b9e5fc3cb00,ON Semi,,+175°C,,,512-FDD5614P,,1,1,,,,,DPAK3,42W,yes,,,,MOSFET,+175°C,-55°C,-1.6V,19ns,7ns
36,2,"R1, R10",100k,,Device:R_Small,Resistor_SMD:R_0603_1608Metric,~,,,,,,,,,,,,,,,,,,,,,,,,,,,,,,,,,,,,,,,,,,,,,,,,,,,,,,
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
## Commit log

2021-03-07 Initial, add mcus
2021-03-07 Work on user io subsystem schematic
2021-03-09 Add f4 decoupling capacitors, add dac, add power converter circuit
2021-03-12 Add submodule
2021-03-12 Finish prototype of DAC/USB/Power system
2021-03-12 Finish screen subsystem
2021-03-12 Export pdf
2021-03-12 Add one more debug connector
2021-03-12 Add mounting holes
2021-03-13 Make updates per suggestions
2021-03-13 Change the side that the resistors are on
2021-03-13 Remove unnecessary photo
2021-03-14 Make most changes for final design
2021-03-14 Update power supply system
2021-03-15 Final iteration before pcb design review
2021-03-15 Finish schematic
2021-03-17 Get everything on board, use buck converter, chnage lm317 footprint
2021-03-17 Decent layout at first glance
2021-03-17 Work on pcb layout
2021-03-18 Replace components
2021-03-19 Huge progress on routing
2021-03-19 Finish initial layout
2021-03-19 Add gerber files
2021-03-19 Documentation for submission
2021-03-24 Update pcb layout
2021-03-24 PCB changes
2021-04-30 Final push
2021-04-30 Update pdf
